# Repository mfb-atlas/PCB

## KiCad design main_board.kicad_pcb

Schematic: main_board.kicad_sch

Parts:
J1: MEGA_SARJ; PhoenixContact_MSTBVA_2,5_4-G-5,08_1x04_P5.08mm_Vertical
J2: POWER; PhoenixContact_MSTBVA_2,5_4-G-5,08_1x04_P5.08mm_Vertical
J3: I2C; PhoenixContact_MSTBVA_2,5_4-G-5,08_1x04_P5.08mm_Vertical
J4: FREE_GPIO; PhoenixContact_MCV_1,5_8-G-3.5_1x08_P3.50mm_Vertical
J5: 5V; PhoenixContact_MSTBVA_2,5_4-G-5,08_1x04_P5.08mm_Vertical
J6: 12V; PhoenixContact_MSTBVA_2,5_4-G-5,08_1x04_P5.08mm_Vertical
J7: 24V; PhoenixContact_MSTBVA_2,5_4-G-5,08_1x04_P5.08mm_Vertical
J8, J9: GND; PhoenixContact_MSTBVA_2,5_4-G-5,08_1x04_P5.08mm_Vertical
J10, J11, J12, J13, J14, J15, J16, J17: Conn_01x02; PhoenixContact_MCV_1,5_2-G-5.08_1x02_P5.08mm_Vertical
MODULE1: 8_RELAY_MODULE
Q1, Q2, Q3, Q4, Q5, Q6, Q7, Q8: PJA3406; SOT-23
R1, R2, R5, R6, R7, R8, R9, R11: 10R; R_0805_2012Metric
R3, R4, R10, R12, R13, R14, R15, R16: 10K; R_0805_2012Metric
U1: BNO055_IMU; IMU_BNO055
U2: TMS570LC43; TI_Eval_Board
U3, U4: CAN_TRANSCEIVER_MODULE; can_transiever_module
U5: Relay_Single

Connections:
+3.3V: U5.2 (COM)
+3V3: U2.J9_3
+5V: J2.1, J3.3, J5.1, J5.2, J5.3, J5.4, U1.1 (Vin), U5.6 (5V)
+12V: J2.2, J6.1, J6.2, J6.3, J6.4
+24V: J2.3, J7.1, J7.2, J7.3, J7.4, J10.2, J11.2, J12.2, J14.2, J16.2, J17.2, Q1.3 (D), Q2.3 (D), Q3.3 (D), Q4.3 (D), Q6.3 (D), Q8.3 (D)
/BUZZER ALARM: J10.1, Q1.1 (S)
/CANH_BMS: U4.5 (CANH)
/CANH_CURTIS: U3.5 (CANH)
/CANL_BMS: U4.6 (CANL)
/CANL_CURTIS: U3.6 (CANL)
/GREEN ALARM: J16.1, Q4.1 (S)
/KAPI_KUMANDA_SW1: J13.2, Q5.3 (D)
/KAPI_KUMANDA_SW2: J13.1, Q5.1 (S)
/PC_ON_HEADER: J15.2, Q7.3 (D)
/PC_ON_HEADER_GND: J15.1, Q7.1 (S)
/RED ALARM: J11.1, Q2.1 (S)
/SARJ START: J1.2, J14.1, Q6.1 (S)
/SWITCH_FREE: J17.1, Q8.1 (S)
/TRANSCEIVER_ON_OFF: U3.1 (3.3V), U4.1 (3.3V), U5.1 (NO)
/YELLOW ALARM: J12.1, Q3.1 (S)
AD2IN_23: J4.5, U2.J9_29
AD2IN_24: J4.6, U2.J9_30
DCAN1RX: U2.J10_44, U4.3 (RX)
DCAN1TX: U2.J10_45, U4.4 (TX)
DCAN2RX: J4.4, U2.J9_12
DCAN2TX: J4.3, U2.J9_13
GIOB_2/DCAN4TX: U2.J10_5, U3.4 (TX)
GIOB_3/DCAN4RX: U2.J10_16, U3.3 (RX)
GND: J1.3, J1.4, J2.4, J3.4, J8.1, J8.2, J8.3, J8.4, J9.1, J9.2, J9.3, J9.4, R3.1, R4.1, R10.1, R12.1, R13.1, R14.1, R15.1, R16.1, U1.3 (GND), U3.2 (GND), U4.2 (GND), U5.5 (GND)
MIBSPI3NCS_2/I2C1_SDA/N2HET1_27/NTZ1_2: J3.1, U1.4 (SDA), U2.J2_8
MIBSPI3NCS_3/I2C1_SCL/N2HET1_29/NTZ1_1: J3.2, U1.5 (SCL), U2.J2_9
N2HET2_0: R9.1, U2.J9_5
N2HET2_1/N2HET1_NDIS: R7.1, U2.J9_6
N2HET2_2/N2HET2_NDIS: J1.1, U2.J9_18
N2HET2_3/MIBSPI2CLK: J4.7, U2.J9_17
N2HET2_4: J4.8, U2.J9_14
N2HET2_6: R8.1, U2.J9_7
N2HET2_7/MIBSPI2NCS_0: R2.1, U2.J9_20
N2HET2_8: R5.1, U2.J10_19
N2HET2_9: R6.1, U2.J9_27
N2HET2_10: R1.1, U2.J9_26
N2HET2_11: J4.2, U2.J9_24
N2HET2_13/MIBSPI2SOMI: R11.1, U2.J10_46
N2HET2_14/MIBSPI2SIMO: U2.J9_22, U5.4 (IN)
N2HET2_22: U2.J9_28
N2HET2_23: J4.1, U2.J9_23
unnamed: Q1.2 (G), R6.2, R12.2
unnamed: Q2.2 (G), R9.2, R15.2
unnamed: Q3.2 (G), R7.2, R13.2
unnamed: Q4.2 (G), R8.2, R14.2
unnamed: Q5.2 (G), R2.2, R4.2
unnamed: Q6.2 (G), R1.2, R3.2
unnamed: Q7.2 (G), R5.2, R10.2
unnamed: Q8.2 (G), R11.2, R16.2

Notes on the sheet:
(J2 P8 YESIL)
(J2 P9 MAVI BEYAZ)
IOS CONNECTION

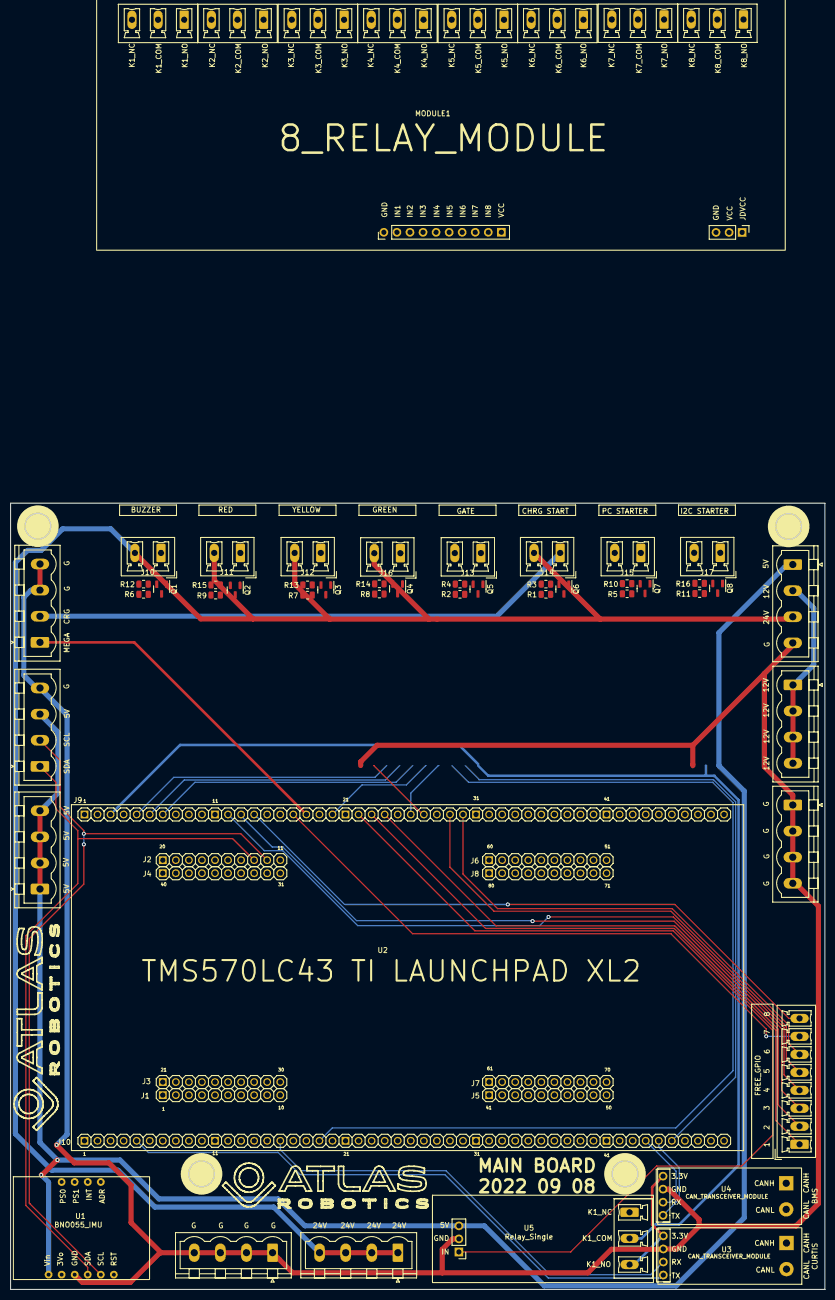
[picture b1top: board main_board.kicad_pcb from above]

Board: 2 copper layers, 158.5 x 153.0 mm, 47 parts (0 on the bottom side), 47 nets.

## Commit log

2022-09-08 uploading documents at the beginning of the project.
2022-09-08 git ignore added
2022-09-08 all pcb design except routing completed.
2022-09-09 pcb to completed gerber completed ready to print the PCB
2022-09-09 distance hole sizes are now smaller (2.5 mm radius)
2022-09-09 gerber files added as rar file
2022-09-12 repo uploaded to remote server first time
2022-09-19 PCB Printed as "MAIN BOARD 2022 09 08"
2022-09-19 Deleting Relays Adding MOSFETs
